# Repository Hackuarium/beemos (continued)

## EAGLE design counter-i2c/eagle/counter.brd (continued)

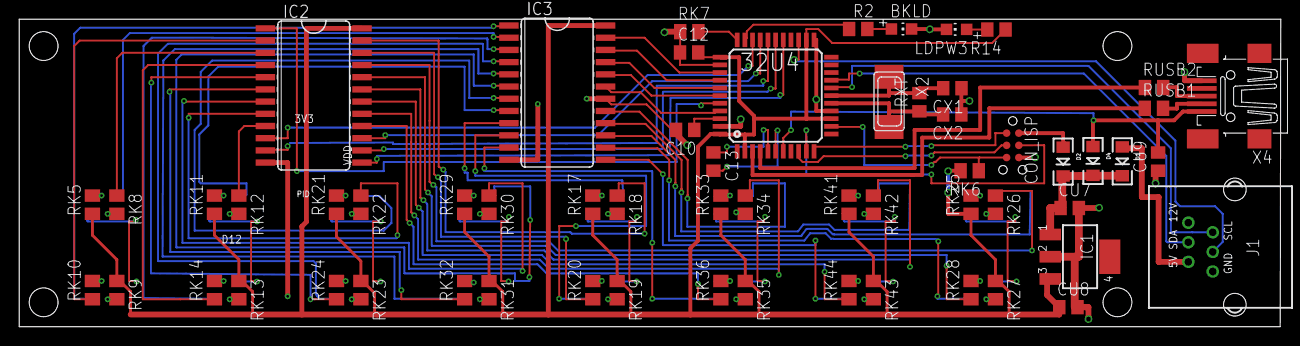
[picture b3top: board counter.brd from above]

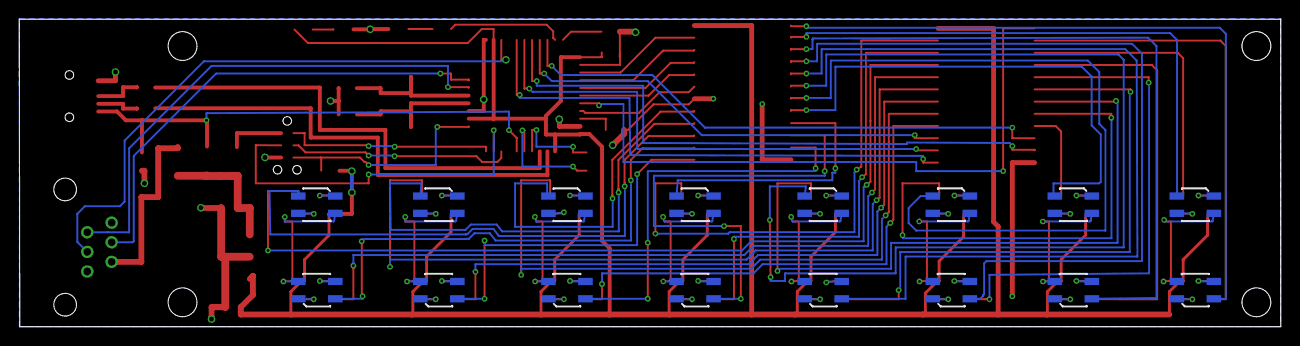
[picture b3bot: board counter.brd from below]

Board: 4 copper layers, 131.3 x 32.0 mm, 76 parts (16 on the bottom side), 100 nets.

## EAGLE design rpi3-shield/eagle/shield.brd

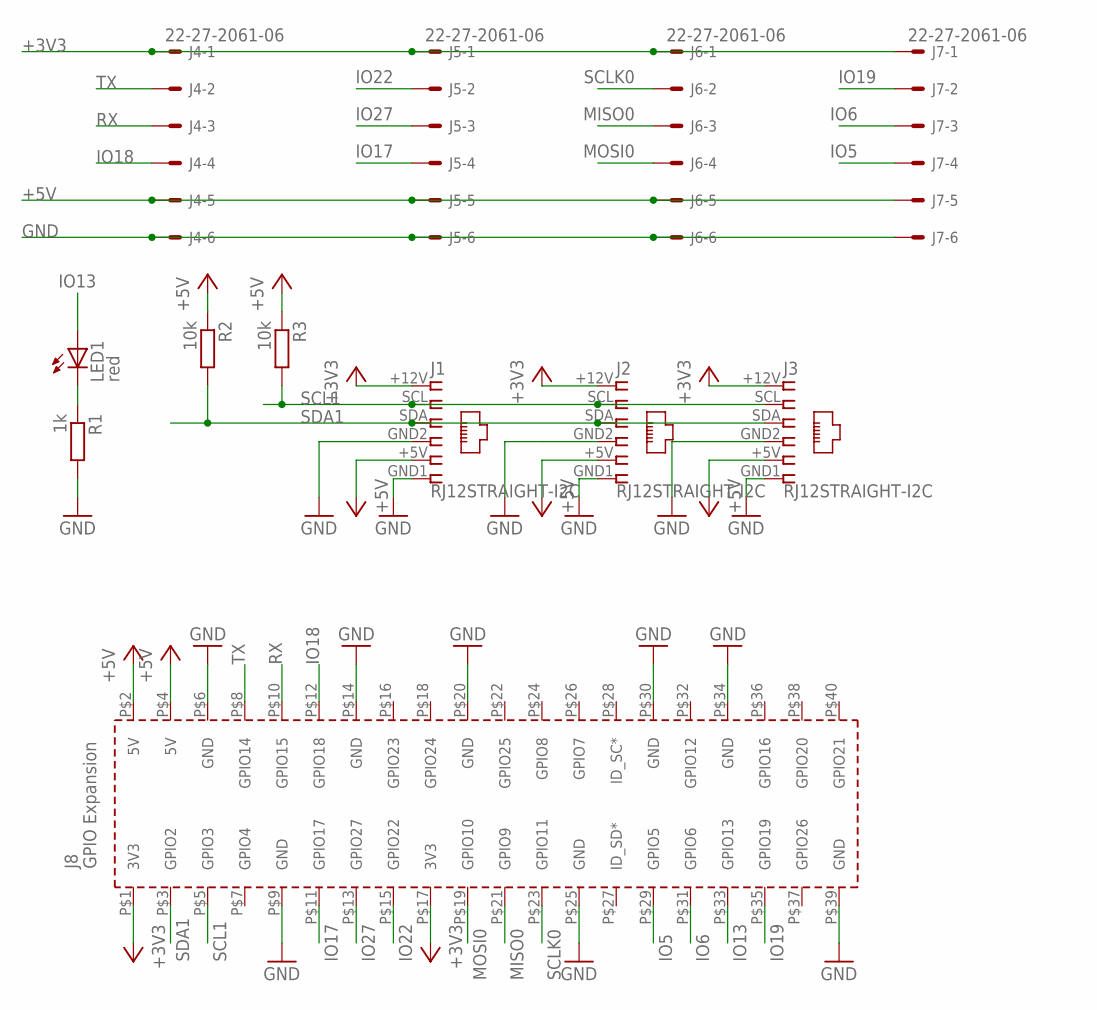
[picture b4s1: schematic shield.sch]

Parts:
J1, J2, J3: RJ12STRAIGHT-I2C; RJ12-STRAIGHT-I2C
J4, J5, J6, J7: 22-27-2061-06; 6410-06
LED1: red; SML0805
PCB1: RPI3RPI3MIRROR; RPI3MIRROR
R1: 1k; R0805
R2, R3: 10k; R0805

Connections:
+3V3: J1.+12V (1), J2.+12V (1), J3.+12V (1), J4.1, J5.1, J6.1, J7.1, PCB1.P$1 (3V3), PCB1.P$17 (3V3)
+5V: J1.+5V (5), J2.+5V (5), J3.+5V (5), J4.5, J5.5, J6.5, J7.5, PCB1.P$2 (5V), PCB1.P$4 (5V), R2.1, R3.1
GND: J1.GND1 (6), J1.GND2 (4), J2.GND1 (6), J2.GND2 (4), J3.GND1 (6), J3.GND2 (4), J4.6, J5.6, J6.6, J7.6, PCB1.P$6 (GND), PCB1.P$9 (GND), PCB1.P$14 (GND), PCB1.P$20 (GND), PCB1.P$25 (GND), PCB1.P$30 (GND), PCB1.P$34 (GND), PCB1.P$39 (GND), R1.2
IO5: J7.4, PCB1.P$29 (GPIO5)
IO6: J7.3, PCB1.P$31 (GPIO6)
IO13: LED1.A, PCB1.P$33 (GPIO13)
IO17: J5.4, PCB1.P$11 (GPIO17)
IO18: J4.4, PCB1.P$12 (GPIO18)
IO19: J7.2, PCB1.P$35 (GPIO19)
IO22: J5.2, PCB1.P$15 (GPIO22)
IO27: J5.3, PCB1.P$13 (GPIO27)
MISO0: J6.3, PCB1.P$21 (GPIO9)
MOSI0: J6.4, PCB1.P$19 (GPIO10)
unnamed: LED1.C, R1.1
RX: J4.3, PCB1.P$10 (GPIO15)
SCL1: J1.SCL (2), J2.SCL (2), J3.SCL (2), PCB1.P$5 (GPIO3), R3.2
SCLK0: J6.2, PCB1.P$23 (GPIO11)
SDA1: J1.SDA (3), J2.SDA (3), J3.SDA (3), PCB1.P$3 (GPIO2), R2.2
TX: J4.2, PCB1.P$8 (GPIO14)

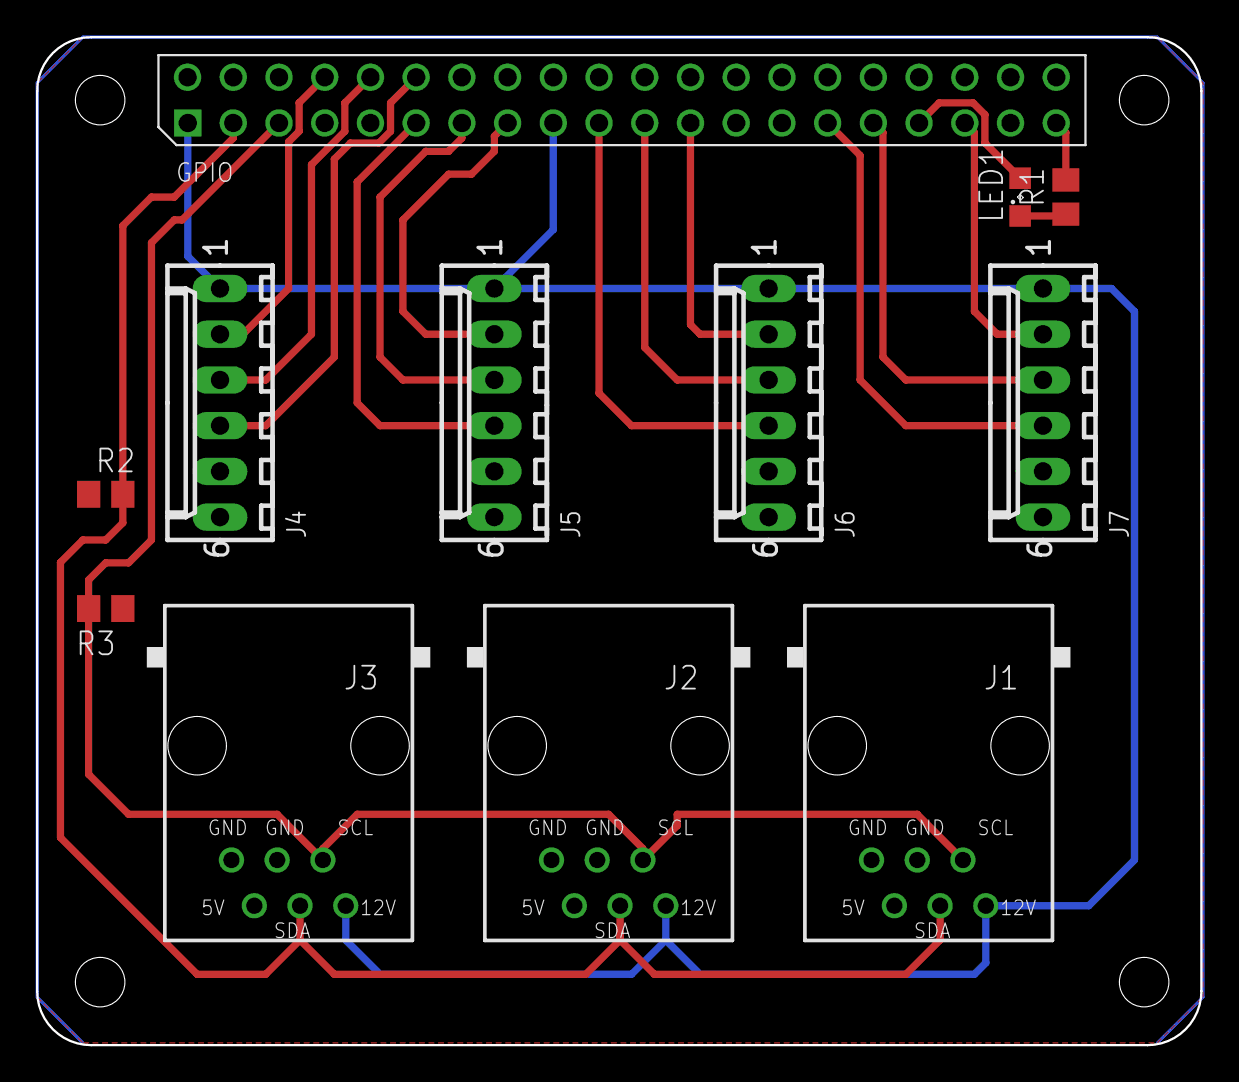
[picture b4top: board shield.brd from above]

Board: 2 copper layers, 64.7 x 56.0 mm, 12 parts (1 on the bottom side), 19 nets.

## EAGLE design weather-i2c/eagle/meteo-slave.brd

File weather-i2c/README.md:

<p align="right">

</p>

# Meteo station I2C

The goal of this project is to create a small board that contains many sensors and that can be used as a meteo station. This board is controlled by the master board and acts as an I2C slave. The board is in sleep mode by default and is only waked up by the master board when it requires data.

## Hardware components

The following components are present on the board:

Microcontroller: ATmega328

Sensors:
* DHT-22 humidity sensor
* DS18B20 for temperature
* Photoresistor for light

Connectors:
* 2X RJ12 to connect other boards via I2C
* 2X 3.5mm jack to eventually connect additional sensors.

## I2C commands

This device appears like a I2C slave at the address XXX and allows the following commands

## Performances
* Consumption in sleep mode: 20µA
* Consumtpion awake: 3.8mA

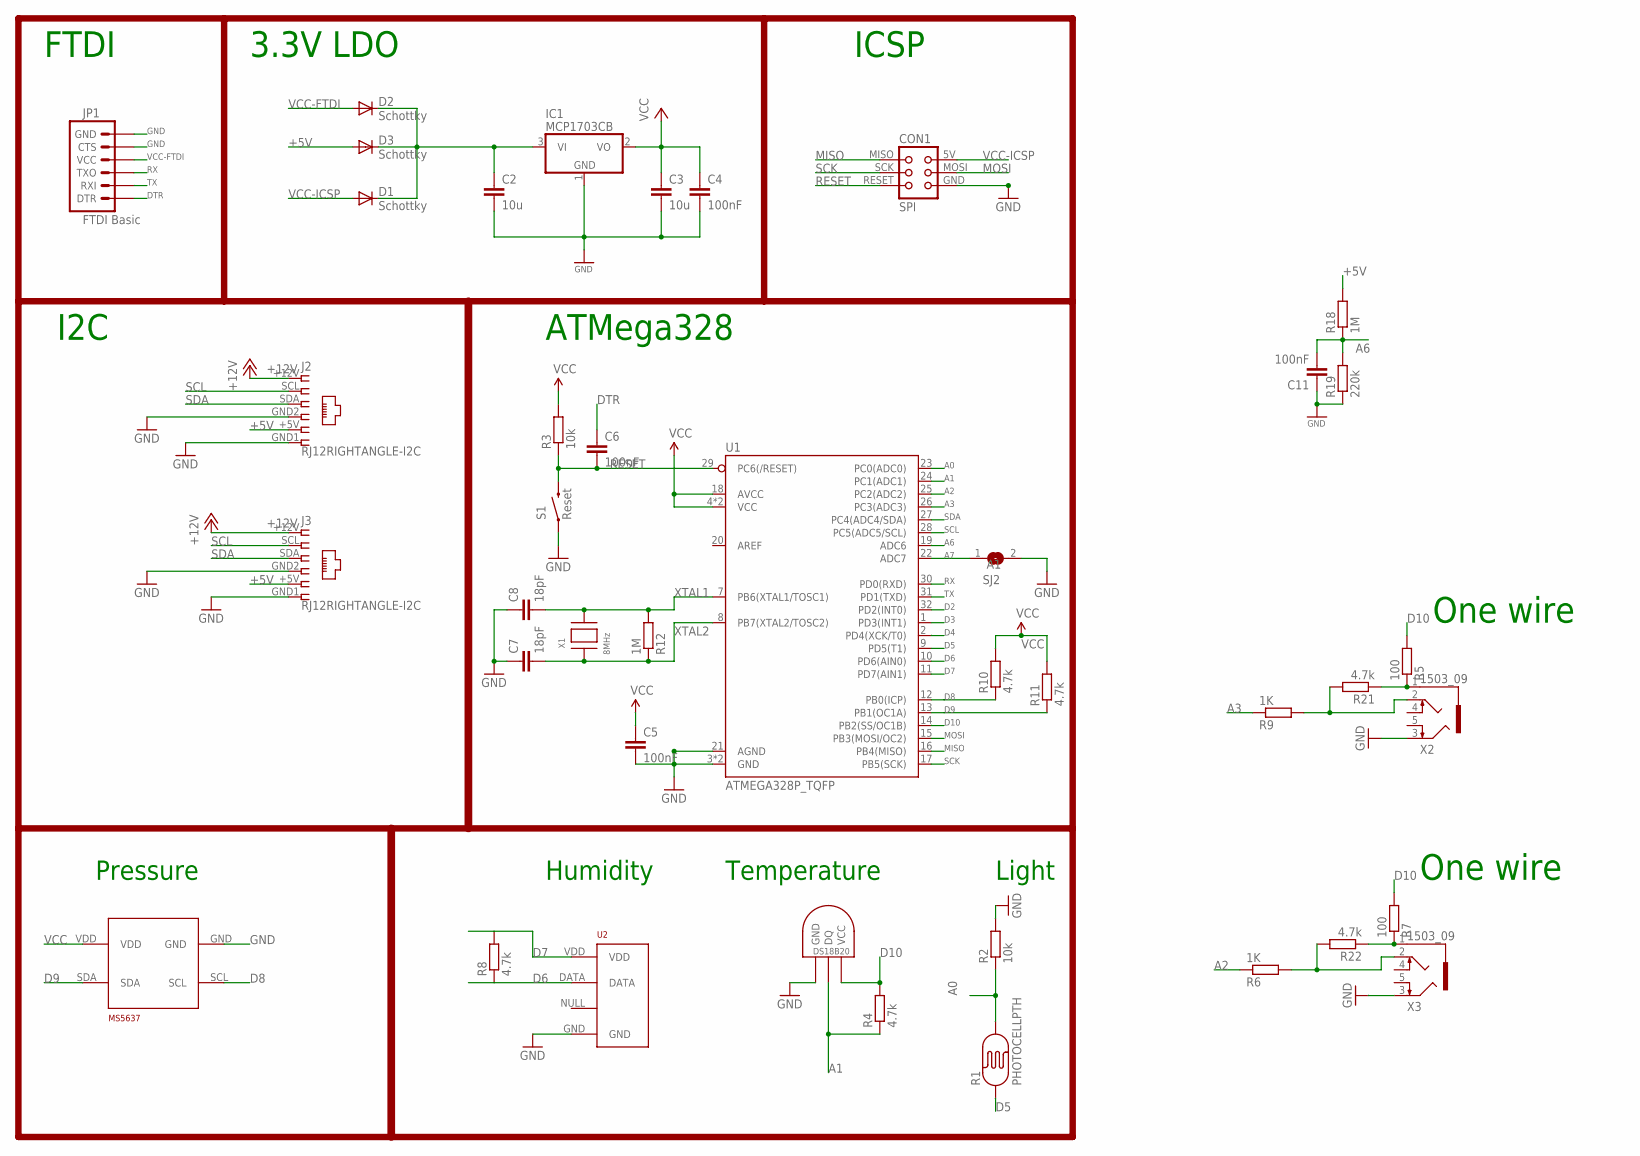
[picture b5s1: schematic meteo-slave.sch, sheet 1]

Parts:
C2, C3: 10u; C0805K; MPN 77-VJ1206V106ZXQTBC; LCSC C15850
C4, C5, C6, C11: 100nF; C0805K; MPN 80-C1206C104K5R; LCSC C49678
C7, C8: 18pF; C0805K; MPN 77-VJ1206A180JXXPBC; LCSC C1797
CON1: SPI; TC2030-MCP
D1, D2, D3: Schottky; SOD123; MPN 621-1N5819HW-F; LCSC C82544
IC1: MCP1703CB; SOT23; LCSC C53352
J2, J3: RJ12RIGHTANGLE-I2C; RJ12-RIGHTANGLE-I2C
JP1: FTDI Basic; 1X06
R1: PHOTOCELLPTH; PHOTOCELL
R2: 10k; R0805
R3: 10k; R0805; LCSC C17513
R4, R8, R10, R11, R21, R22: 4.7k; R0805
R5, R7: 100; R0805
R6, R9: 1K; R0805
R12, R18: 1M; R0805; LCSC C17514
R19: 220k; R0805; LCSC C17514
S1: Reset; TACTILE-SWITCH-SMD-ALT01
SJ2: A1; SJ
U1: ATMEGA328P_TQFP; TQFP32-08
U2: RHT03_DHT-22_AM2302; RHT03_DHT-22
U$1: DS1820TO92; DS1820
U$19: MS5637WIDE
X1: 8MHz; NX6035; MPN 729-F60800010; LCSC C122522
X2, X3: 1503_09

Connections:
+5V: D3.A, J2.+5V (5), J3.+5V (5), R18.2
+12V: J2.+12V (1), J3.+12V (1)
+XV: C2.1, D1.C, D2.C, D3.C, IC1.3 (VI)
A0: R1.2, R2.1, U1.23 (PC0(ADC0))
A1: R4.1, U1.24 (PC1(ADC1)), U$1.DQ
A2: R6.1, U1.25 (PC2(ADC2))
A3: R9.1, U1.26 (PC3(ADC3))
A6: C11.2, R18.1, R19.2, U1.19 (ADC6)
A7: SJ2.1, U1.22 (ADC7)
D2: U1.32 (PD2(INT0))
D3: U1.1 (PD3(INT1))
D4: U1.2 (PD4(XCK/T0))
D5: R1.1, U1.9 (PD5(T1))
D6: R8.1, U1.10 (PD6(AIN0)), U2.DATA
D7: R8.2, U1.11 (PD7(AIN1)), U2.VDD
D8: R10.1, U1.12 (PB0(ICP)), U$19.SCL
D9: R11.1, U1.13 (PB1(OC1A)), U$19.SDA
D10: R4.2, R5.2, R7.2, U1.14 (PB2(SS/OC1B)), U$1.VDD (VCC)
DTR: C6.1, JP1.1 (DTR)
GND: C2.2, C3.2, C4.2, C5.2, C7.1, C8.1, C11.1, CON1.GND, IC1.1 (GND), J2.GND1 (6), J2.GND2 (4), J3.GND1 (6), J3.GND2 (4), JP1.5 (CTS), JP1.6 (GND), R2.2, R19.1, S1.1, S1.2 (1), SJ2.2, U1.3 (GND), U1.5 (GND), U1.21 (AGND), U2.GND, U$1.GND, U$19.GND, X2.3, X3.3
MISO: CON1.MISO, U1.16 (PB4(MISO))
MOSI: CON1.MOSI, U1.15 (PB3(MOSI/OC2))
unnamed: R6.2, R22.2, X3.2
unnamed: R7.1, R22.1, X3.1
unnamed: R5.1, R21.1, X2.1
unnamed: R9.2, R21.2, X2.2
RESET: C6.2, CON1.RESET, R3.1, S1.3 (2), S1.4 (2), U1.29 (PC6(/RESET))
RX: JP1.3 (TXO), U1.30 (PD0(RXD))
SCK: CON1.SCK, U1.17 (PB5(SCK))
SCL: J2.SCL (2), J3.SCL (2), U1.28 (PC5(ADC5/SCL))
SDA: J2.SDA (3), J3.SDA (3), U1.27 (PC4(ADC4/SDA))
TX: JP1.2 (RXI), U1.31 (PD1(TXD))
VCC: C3.1, C4.1, C5.1, IC1.2 (VO), R3.2, R10.2, R11.2, U1.4 (VCC), U1.6 (VCC), U1.18 (AVCC), U$19.VDD
VCC-FTDI: D2.A, JP1.4 (VCC)
VCC-ICSP: CON1.5V (VCC), D1.A
XTAL1: C8.2, R12.2, U1.7 (PB6(XTAL1/TOSC1)), X1.P$2
XTAL2: C7.2, R12.1, U1.8 (PB7(XTAL2/TOSC2)), X1.P$1

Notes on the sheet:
ICSP
ATMega328
3.3V LDO
I2C
FTDI
Light
Temperature
Humidity
Pressure
One wire

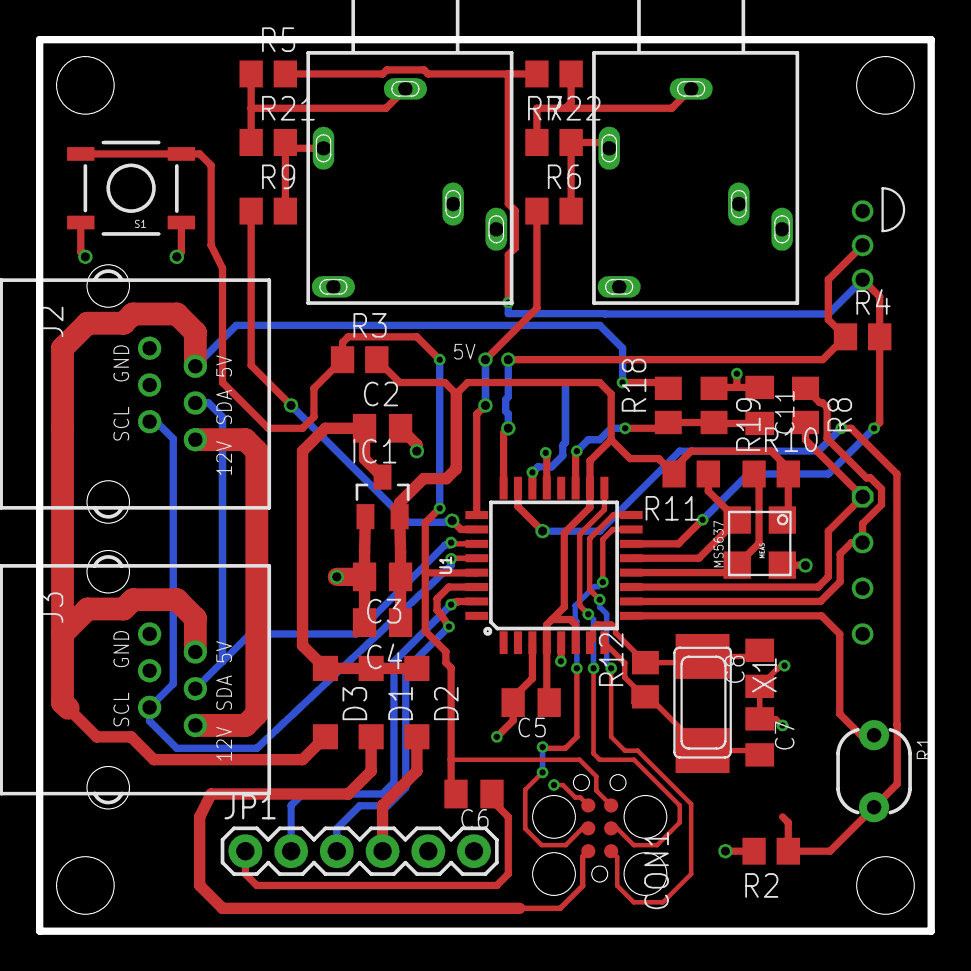
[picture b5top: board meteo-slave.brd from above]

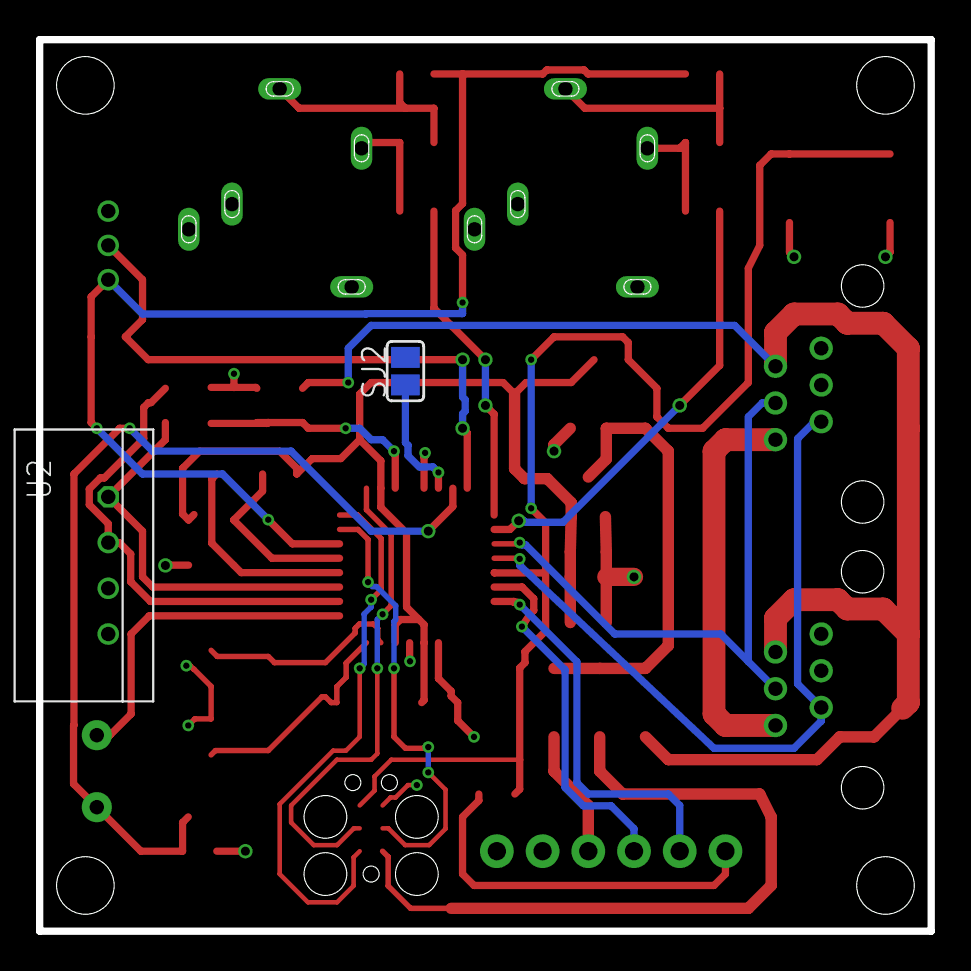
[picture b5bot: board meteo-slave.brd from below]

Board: 2 copper layers, 49.5 x 49.5 mm, 41 parts (2 on the bottom side), 34 nets.

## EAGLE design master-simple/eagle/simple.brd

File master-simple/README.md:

<p align="right">

</p>

# Master board
This board is connected to all other modules via i2c and sends all the data to a remote server using a SIM card. It also uses a temperature sensor to monitor the internal temperature of the hive. 

_We are currently using a simplified version of the Master board for debugging purpose. A more complete version with the temperature sensor will come later and is in development._

## Components
* x1 Microprocessor Atmel 32u4 (similar to Arduino Leonardo boards), 8Mhz, 3.3V
* x3 RJ12 connectors

## Performances

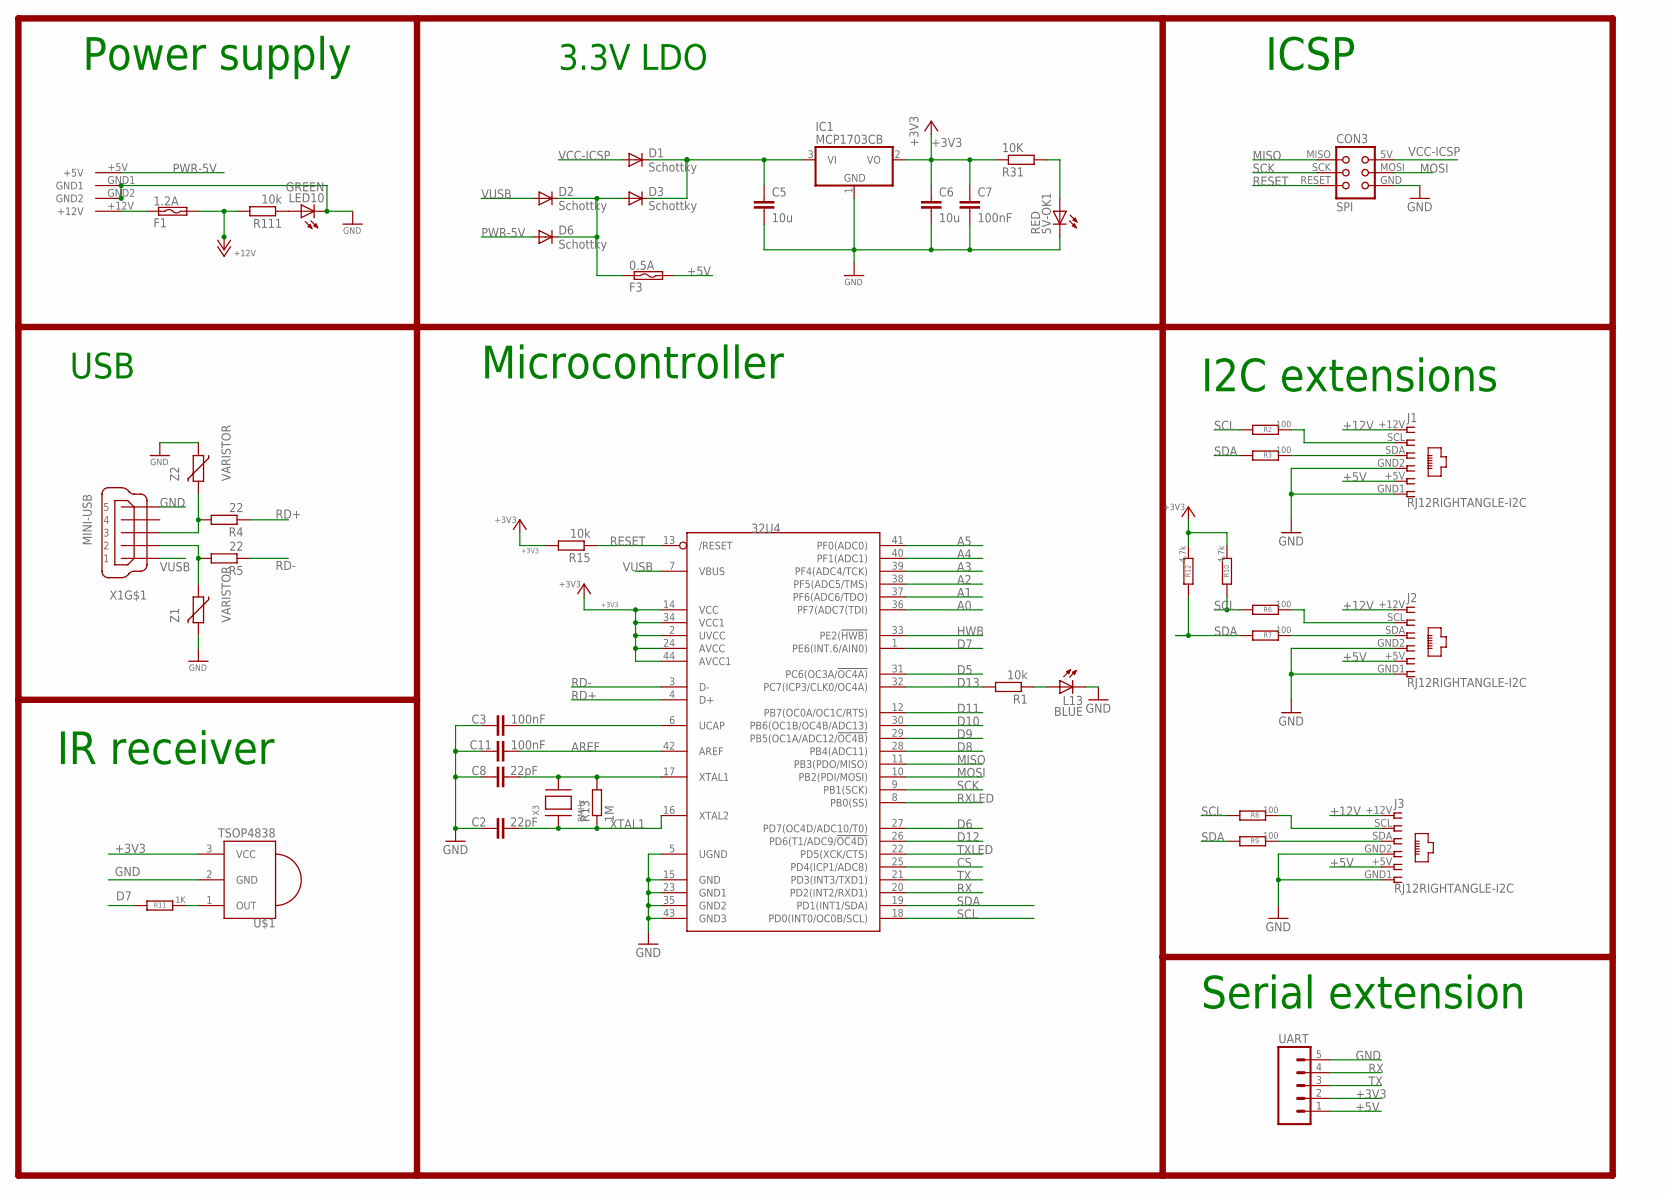
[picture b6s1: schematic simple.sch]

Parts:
5V-OK1: RED; CHIP-LED0805
C2, C8: 22pF; C0805K
C3, C11: 100nF; C0805K
C5, C6: 10u; C0805K; MPN 77-VJ1206V106ZXQTBC; LCSC C15850
C7: 100nF; C0805K; MPN 80-C1206C104K5R; LCSC C49678
CON3: SPI; TC2030-MCP-NL
D1, D2, D3, D6: Schottky; SOD123; MPN 621-1N5819HW-F; LCSC C82544
F1: 1.2A; C1812
F3: 0.5A; C1812
IC1: MCP1703CB; SOT23; LCSC C53352
J1, J2, J3: RJ12RIGHTANGLE-I2C; RJ12-RIGHTANGLE-I2C
L13: BLUE; CHIP-LED0805
LED10: GREEN; CHIP-LED0805
R1, R15: 10k; M0805
R2, R3, R6, R7, R8, R9: 100; R0805
R4, R5: 22; R0805; LCSC C17561
R10, R12: 4.7k; R0805
R11: 1K; R0805
R13: 1M; M0805
R31: 10K; R0805
R111: 10k; R0805
U$1: TSOP4838; PNA460XM
U$4: 32U4; TQFP44
U$6: KPJX-4S-S
UART: M05PTH; 1X05
X1: MINI-USB; 32005-201; MPN 649-10033526-N3212LF; LCSC C46391
X3: 8MHz; NX6035
Z1, Z2: VARISTOR; CT/CN0603

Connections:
+3V3: C6.1, C7.1, IC1.2 (VO), R10.1, R12.1, R15.2, R31.1, U$1.3 (VCC), U$4.2 (UVCC), U$4.14 (VCC), U$4.24 (AVCC), U$4.34 (VCC1), U$4.44 (AVCC1), UART.2
+5V: F3.2, J1.+5V (5), J2.+5V (5), J3.+5V (5), UART.1
+12V: F1.2, J1.+12V (1), J2.+12V (1), J3.+12V (1), R111.2
+XV: C5.1, D1.C, D3.C, IC1.3 (VI)
A0: U$4.36 (PF7(ADC7(TDI))
A1: U$4.37 (PF6(ADC6/TDO))
A2: U$4.38 (PF5(ADC5/TMS))
A3: U$4.39 (PF4(ADC4/TCK))
A4: U$4.40 (PF1(ADC1))
A5: U$4.41 (PF0(ADC0))
AREF: C11.1, U$4.42 (AREF)
CS: U$4.25 (PD4(ICP1/ADC8))
D5: U$4.31 (PC6(OC3A/!OC4A))
D6: U$4.27 (PD7(OC4D/ADC10/T0))
D7: R11.2, U$4.1 (PE6(INT.6/AIN0))
D8: U$4.28 (PB4(ADC11))
D9: U$4.29 (PB5(OC1A/ADC12/!OC4B))
D10: U$4.30 (PB6(OC1B/OC4B/ADC13))
D11: U$4.12 (PB7(OC0A/OC1C/RTS))
D12: U$4.26 (PD6(T1/ADC9/!OC4D))
D13: R1.2, U$4.32 (PC7(ICP3/CLK0/OC4A))
GND: 5V-OK1.C, C2.1, C3.1, C5.2, C6.2, C7.2, C8.1, C11.2, CON3.GND, IC1.1 (GND), J1.GND1 (6), J1.GND2 (4), J2.GND1 (6), J2.GND2 (4), J3.GND1 (6), J3.GND2 (4), L13.C, LED10.C, U$1.2 (GND), U$4.5 (UGND), U$4.15 (GND), U$4.23 (GND1), U$4.35 (GND2), U$4.43 (GND3), U$6.GND1, U$6.GND2, UART.5, X1.5, Z1.2, Z2.1
HWB: U$4.33 (PE2(!HWB))
MISO: CON3.MISO, U$4.11 (PB3(PDO/MISO))
MOSI: CON3.MOSI, U$4.10 (PB2(PDI/MOSI))
unnamed: J2.SCL (2), R6.1
unnamed: J1.SCL (2), R2.1
unnamed: J1.SDA (3), R3.1
unnamed: L13.A, R1.1
unnamed: D2.C, D3.A, D6.C, F3.1
unnamed: J2.SDA (3), R7.1
unnamed: J3.SCL (2), R8.1
unnamed: J3.SDA (3), R9.1
unnamed: R11.1, U$1.1 (OUT)
unnamed: 5V-OK1.A, R31.2
unnamed: C3.2, U$4.6 (UCAP)
unnamed: F1.1, U$6.+12V
unnamed: C8.2, R13.2, U$4.17 (XTAL1), X3.P$2
unnamed: LED10.A, R111.1
PWR-5V: D6.A, U$6.+5V
RD+: R4.1, U$4.4 (D+)
RD-: R5.1, U$4.3 (D-)
RESET: CON3.RESET, R15.1, U$4.13 (/RESET)
RX: U$4.20 (PD2(INT2/RXD1)), UART.4
RXLED: U$4.8 (PB0(SS))
SCK: CON3.SCK, U$4.9 (PB1(SCK))
SCL: R2.2, R6.2, R8.2, R10.2, U$4.18 (PD0(INT0/OC0B/SCL))
SDA: R3.2, R7.2, R9.2, R12.2, U$4.19 (PD1(INT1/SDA))
TX: U$4.21 (PD3(INT3/TXD1)), UART.3
TXLED: U$4.22 (PD5(XCK/CTS))
USBC_N: R5.2, X1.2, Z1.1
USBC_P: R4.2, X1.3, Z2.2
VCC-ICSP: CON3.5V (VCC), D1.A
VUSB: D2.A, U$4.7 (VBUS), X1.1
XTAL1: C2.2, R13.1, U$4.16 (XTAL2), X3.P$1

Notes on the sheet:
IR receiver
ICSP
Microcontroller
USB
3.3V LDO
Power supply
Serial extension
I2C extensions

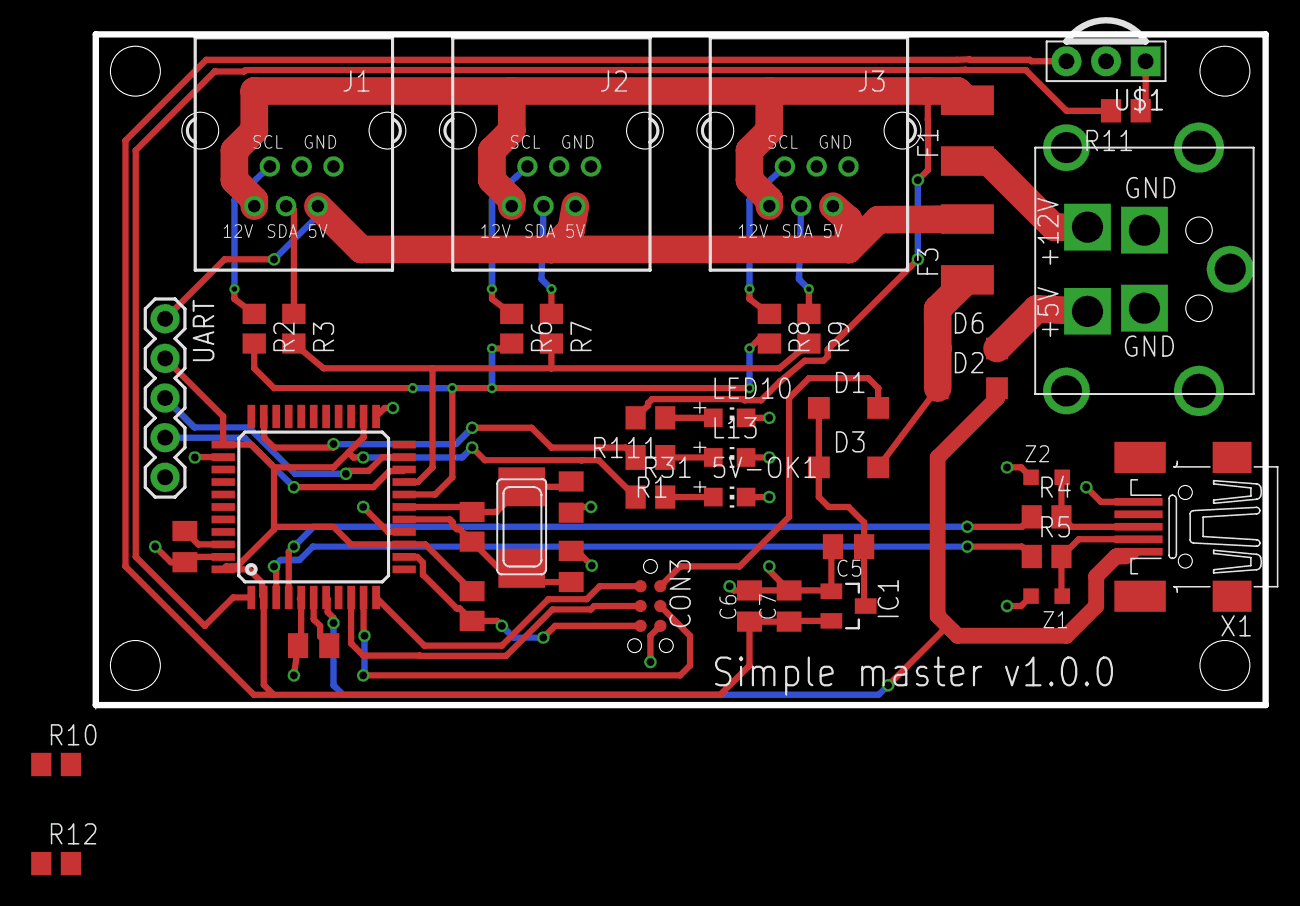
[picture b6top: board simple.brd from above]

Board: 2 copper layers, 75.0 x 43.0 mm, 45 parts (0 on the bottom side), 38 nets.

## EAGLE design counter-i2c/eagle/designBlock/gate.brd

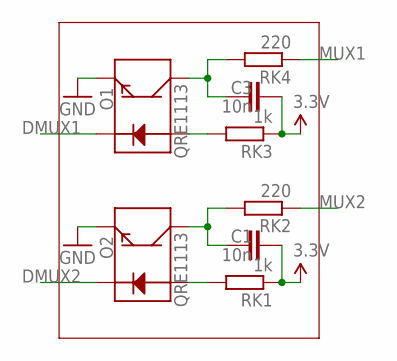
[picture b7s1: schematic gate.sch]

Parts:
C1, C3: 10n; C0805
O1, O2: QRE1113
RK1, RK3: 1k; M0805
RK2, RK4: 220; M0805

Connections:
3.3V: C1.2, C3.2, RK1.1, RK3.1
DMUX1: O1.2 (K)
DMUX2: O2.2 (K)
GND: O1.4 (E), O2.4 (E)
MUX1: RK4.1
MUX2: RK2.1
RD1: O1.1 (A), RK3.2
RD2: O2.1 (A), RK1.2
Y1: C3.1, O1.3 (C), RK4.2
Y2: C1.1, O2.3 (C), RK2.2

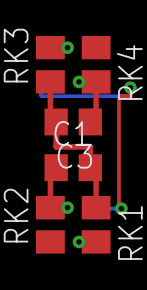
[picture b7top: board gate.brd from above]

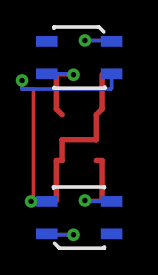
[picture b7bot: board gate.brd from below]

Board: 2 copper layers, 8 parts (2 on the bottom side), 6 nets.

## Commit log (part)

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2017-04-30 PCB prototype
2017-05-20 counter
2017-05-20 work in progress
2017-05-30 Places 16 IR LED emitter/receptors on board layout with defined distances, other parts can me moved to layout board.
2017-07-23 Routing partial
2017-07-23 add custom library for a gate
2017-07-23 add gitignore
2017-07-23 update custom library
2017-07-26 update library to fix small via bug
2017-07-26 set 74HC154D to gnd
2017-07-29 add new design
2017-07-29 clean up
2017-07-30 work in progress on slaveMeteo
2017-08-14 first version of counter for production
2017-09-30 refactor
2018-02-09 commented testOut and corrected mistake in binary values
2018-02-23 first version with content
2018-02-27 ajout fonction in, definition pin in
2018-02-27 added openscad schematic
2018-03-13 Started FreeCAD project and designed PCB floor for the enclosure
2018-03-20 designed side walls for the enclosure
2018-03-27 finished designing beemos enclosure in freeCAD
2018-04-07 corrected enclosure plancs to correctly change with thickness
2018-04-10 realigned opening for USB port and adapted other parts accordingly
2018-04-19 reorganized directories and incorporated beemos-master into the repository
2018-04-20 updated eagle libraries and readme, started designing meteo station
2018-04-21 working on i2c-slave basic board
2018-04-21 improve port mapping doc
2018-04-21 create slaves-i2c folder
2018-04-21 connected components on Slave meteo. Kept backup in case we still need a sound detector
2018-04-21 reorganized components oon brd file for meteoslave
2018-04-21 finish slave-basic
2018-04-21 add folder for lcd-screen
2018-04-22 redesigned meteoSlave using slave-basic
2018-04-22 moved all slaves to slave folder
2018-04-22 add documentation and move lcd-screen
2018-04-22 rename lcd-slave and add address selector
2018-04-22 rename slave readme for lcd-slave
2018-04-22 add address select in description
2018-04-22 standardised file and folder names for meteo-slave
2018-04-22 add cam processor for eagle staring 8.6
2018-04-22 add crystal to bard
2018-04-22 working on a simple master
2018-04-23 finalize first version of master-simple
2018-04-23 update cam processor to deal correcty with drill
2018-04-23 fix file names
2018-04-23 add info in slaves README
2018-04-23 improve docs for slaves
2018-04-23 update meteo
2018-04-24 Added LoRa and OneWire to schematics
2018-05-06 change resistor for led
2018-05-06 remove 10nf capacitor
2018-05-06 change resistor to 1k
2018-05-06 add label on doors
2018-05-06 working on arduino test program
2018-05-06 working example of counter
2018-05-06 add multithred
2018-05-06 activate the logger
2018-05-07 fix log to enable 27 logs every 1h
2018-05-08 Add luminosity and improve logger
2018-05-08 add docs folder
2018-05-08 add one wire on SCL
2018-05-08 add docs on RJ12 hacking for testing
2018-05-08 PCB soldering doc v1.0
2018-05-08 increasing IR detector pad size
2018-05-09 Updated counter doc, new box design in FreeCAD (fixations for gates on main floor, bigger board compartment to include RJ12 socket, new hole for RJ12 socket and also below it to ensure board is flat 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
2018-05-10 Added image with soldering steps, changed some text
2018-05-10 Restructured doc folders
2018-05-10 Delete BeeCounter.md
    Moved to BeeCounter folder
2018-05-10 Rename BeeCounter_soldering.md to README.md
2018-05-11 Added IR beams picture from phone camera, edited doc text
2018-05-12 Added fixation for side walls, re-exported dxf file
2018-05-13 remove meteo capacitor for AREF
2018-05-14 Modified holes from side wall for USB and RJ12, corrected location of fixations on ceiling, changed size of front/back wall cover
2018-05-14 Removed old files
2018-05-14 Backlink to CADLAB.io has been added.
2018-05-16 add test to check the fuse
2018-05-16 start docs about atmeaga328 do-it-yourself
2018-05-16 add i2c slave process to counter
2018-05-16 move address selector pad in meteo board
2018-05-16 add meteo temperature test code
2018-05-17 meteo-slave: add voltage monitoring of i2c
2018-05-17 meteo-slave: change light control to use internal pullup
2018-05-17 invert detection
2018-05-19 move files for meteo-i2c
2018-05-19 meteo-i2c: add test for DHT-22
2018-05-19 meteo-i2c: add libraries and use local one
2018-05-19 revert to resistor for LDR to be able to tune
2018-05-19 master-simple: add arduino code
2018-05-19 meteo-i2c: add docs about consumption
2018-05-19 meteo-i2c: add tests
2018-05-19 meteo-i2c: remove wrong test
2018-05-20 arduino$: improve hack library
2018-05-20 rename meteo-i2c to weather-i2c
2018-05-20 master-simple: enable watch dog
2018-05-20 master-simple: enable wire master
2018-05-20 weather-i2c: rename arduino project to weather
2018-05-20 counter-i2c: move openscad files
2018-05-20 counter-i2c: move arduino code to right folder
2018-05-20 weather-i2c: improve i2c test to send random data
2018-05-21 master-simple: correct lib link
2018-05-21 master-simple: add soft i2c library
2018-05-21 weather-i2c: improve program to get data and sleep
2018-05-21 master-simple: add demo for weather data retrieval
2018-05-21 master-simple: improve wakeupFromWire test case
2018-05-22 Write one README for each board and refactor directories
2018-05-23 weather-i2c: modify sleep test
2018-05-26 add working examples of sim800l
2018-05-28 weather-slave: add 4.7k for humidity sensor
2018-05-28 weather-slave: add annotation for pressure sensor
2018-05-29 Reorganized components, placement. Cleanup of temporary files
2018-05-29 Changed side of RJ12 connectors
2018-05-29 clean DHT adafruit library to reduce memory usage
2018-05-29 weather-i2c: cleanup v1.1
2018-05-29 Almost finished beemos master board (labels to do still)
2018-05-30 Repositioned labels on the board layout
2018-05-30 Added octopus logo (right sides of board?)
2018-06-02 master-simple: add image for sim800l connection
2018-06-05 add node script for rpi
2018-06-05 add gas
2018-06-05 weather-i2c: tune memory
2018-06-05 master: cleanup
2018-06-08 Arranged labels and resistors in beemos master board layout
2018-06-08 Fixed airwires/clearance for beemos master board
2018-06-09 Added power/com LEDs, extra pins exposed, cristal symmetric
2018-06-09 Updated schematic with LEDs
2018-06-09 Minor label changes
2018-06-09 improve counter to remove min/max and add debug
2018-06-09 small menu improvement for gate monitoring
2018-06-09 Labels positioned scale board
2018-06-09 final scale version
2018-06-10 spared 16 bytes in test DHT library
2018-06-12 rename test directory for counter to be arduinoIDE-compliant
2018-06-14 Create images folder and put logo
2018-06-14 Corrects .PNG to .png for logo
2018-06-14 Add vectorial logo file in svg format
2018-06-14 remove old logo
2018-06-14 changed logo to svg in README.md
2018-06-14 Set theme jekyll-theme-hacker
2018-06-15 Set theme jekyll-theme-leap-day
2018-06-15 Add pictures
2018-06-15 Write french README. Add links to PCB docs and to change language.
2018-06-15 Fix newline in README section. Backlink to main README from Counter README
2018-06-15 Try backlink to main page using pure HTML
2018-06-15 fix relative path to logo in counter README
2018-06-15 Use online image path from github in counter README
2018-06-15 added backlink to all READMEs
2018-06-15 format detailed counter reame. move all eagle files for weather-i2c and update readme.
2018-06-15 correct typos in images path for README
2018-06-15 fix images width for README
2018-06-26 move master board to master folder
2018-06-26 add scale readme
2018-06-26 add HX711 in project tree and load locally
2018-06-26 add testcases for master board
2018-06-26 rename not used gprs code
2018-06-27 add local copy of HX711 library
2018-07-24 finish drawerFloor
2018-07-29 fix the +3.3V
2018-07-29 add weight test
2018-07-29 correct resistor for voltage check
2018-07-29 scale-i2c: add voltage test
2018-07-29 weather-i2c: fix voltage check resistor value
2018-07-29 move hackuarium arduino lib to submodule
2018-07-29 scale-i2c: add arduino program with multithread
2018-07-29 scale-i2c: add docs
2018-07-29 scale-i2c: allow calibration over i2c and improve docs
2018-07-29 scale-i2c: working version
2018-07-29 rpi3-shield: working on a RPi3 shield
2018-07-30 change libino to https links
2018-07-31 rpi3-shield: v1.0.0 submitted for production
2018-08-04 add master arduino code
2018-08-04 master: add test gprs thread
2018-08-13 Updated submodules
2018-08-13 improve userguide of scale
2018-08-13 (scale-i2c): add some parameters in the docs
2018-08-14 master: add docs
2018-08-14 master: fix logs
2018-08-14 update main README
2018-08-14 master: fix link in docs
2018-08-14 add picture of master in readme
2018-08-16 Update README.md
    update of state of the project
2018-08-17 counter-i2c: add more debug info
2018-08-17 update of the counter readme
2018-08-17 update of counter readme
2018-08-17 adding pictures to the counter readme
2018-08-22 counter: migrate code to libino
2018-08-22 counter: remove unusted counter files
2018-08-22 master: improve memory test code
2018-08-22 master: correct logger delay and writelog after format
2018-08-22 master: change parameters to load counter data
2018-08-23 master: remove delay for i2c copy slave and more memory
2018-08-25 Add load cell wiring picture
2018-08-25 Replace image load cell wiring
2018-08-25 remove old load cell wiring picture
2018-08-25 master: add new humidity sensor Li7021
2018-08-26 update libino
2018-08-26 scale: remove useless variables
2018-08-26 scale: add resetCounter, BA command from I2C
2018-08-26 scale: change I2C register
2018-08-26 weater: add vscode arduino configuraiton
2018-08-26 master: add vscode arduino configuration
2018-08-28 Create tobedeleted
2018-08-28 adding pictures of scales & experiments
2018-08-28 adding pictures of the counter experiment
2018-08-28 adding pictures of scales
2018-08-28 adding picture of scale 2 assembled
2018-08-28 master: fix parameter for logging interval
2018-08-28 close #19
2018-08-29 master: update submodule and use SoftWire library
2018-08-29 master: working on version 1.1 of PCB
2018-08-29 master: pcb version 1.1
2018-09-03 update counter for version 1.1 and possibility to disable light emission
2018-09-04 add picture of IR sensors orientation
2018-09-04 Modify entry height, move sensor further from edge
2018-09-04 Add dfx file for boxCounter
2018-09-05 add thread protection for wire communication
2018-09-05 master: remove protect / unprotect
2018-09-06 Make 5mm wider, adjust, add small extension, add hole below RJ11 connector, gates 7mm instead of 9mm and adjust
2018-09-06 Reposition pieces, make smaller extension on front/rear walls
2018-09-07 update libino and change number of logs in master multilog
2018-09-07 fix libino release bug
2018-09-08 counter: desactivate log and clear log
2018-09-08 master: correct indentation
2018-09-09 counter: add test results
2018-09-09 counter: reset correctly the board
2018-09-09 counter: turn on / off led just before / after
2018-09-09 counter: correct indentation of TotalUtilities
2018-09-09 counter: correct the description of background experiment
2018-09-09 counter: add non processed data
2018-09-09 counter: update tests description
2018-09-11 Update of counter box, single hole for RJ11 connector and pins, elongates front and back wall
2018-09-11 Update svg file according to FCstd
2018-09-11 add new test results for counter
2018-09-13 Add test for Si7021 in weather-i2c folder
2018-09-15 counter: update distance results
2018-09-15 counter: add BG in parameters AA->AP
2018-09-15 master: allow to copy counter BG parameter
2018-09-15 update counter read me
2018-09-16 create cad subdirectory
2018-09-16 adding scale box
2018-10-09 update 2 readme FR
2018-10-23 Longer tunnel (+20mm) and associated parts
2019-01-06 Change rotary encoder pinout to use interruptible pins on Atmega328p
2019-01-08 check humidity every 60s excepts if fail
2019-01-08 add sleep test for master
2019-01-08 disable / enable ADC in sleep mode
2019-04-04 Adjust and add holes in ceiling + corresponding holes on L/R
2019-04-18 Update path in libino Wire, log gate8in/out (don't log background anymore)
2019-07-09 add .vscode in gitignore
2019-07-09 MQQT test
2019-07-09 working on esp8266 software
2019-07-09 add parameters
2021-07-15 chore: update libino
